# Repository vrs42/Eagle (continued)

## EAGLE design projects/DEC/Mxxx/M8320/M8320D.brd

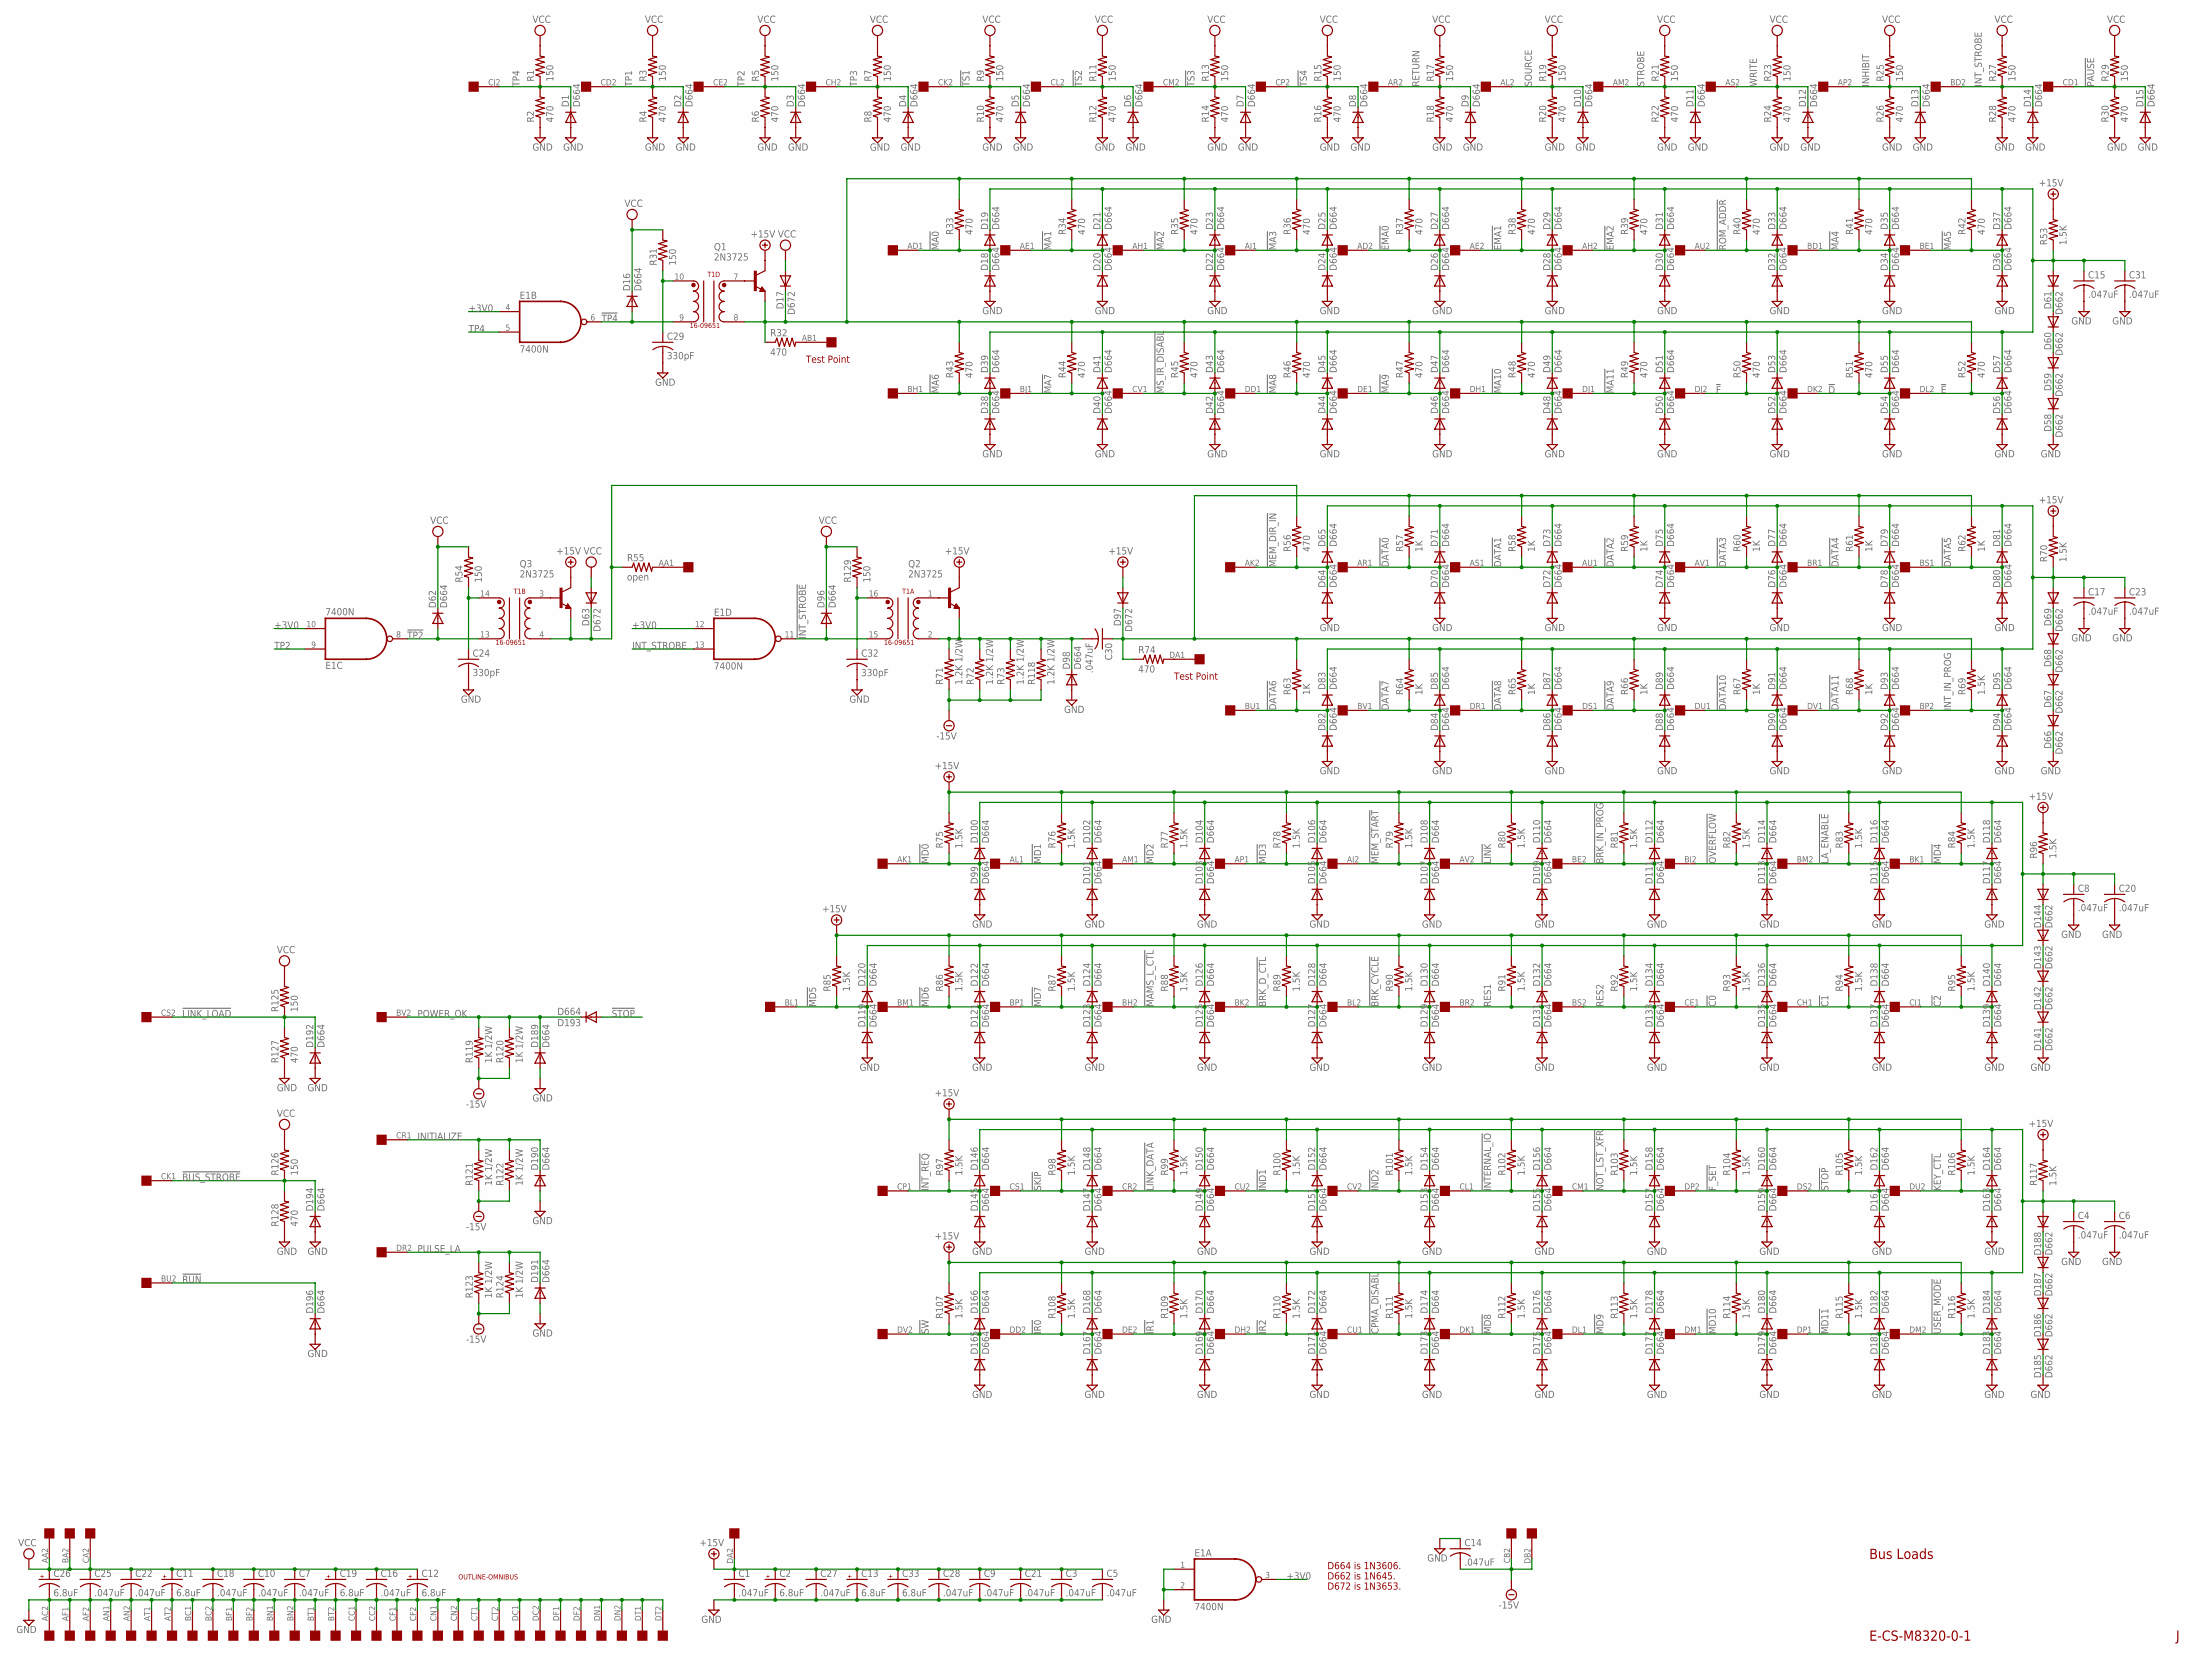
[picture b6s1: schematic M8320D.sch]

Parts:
C1, C3, C4, C5, C6, C7, C8, C9, C10, C14, C15, C16, C17, C18, C20, C21, C22, C23, C25, C27, C28, C30, C31: .047uF; C063-025X075
C2, C11, C12, C13, C19, C26, C33: 6.8uF; E12-8
C24, C29, C32: 330pF; C063-025X075
D1, D2, D3, D4, D5, D6, D7, D8, D9, D10, D11, D12, D13, D14, D15, D16, D18, D19, D20, D21, D22, D23, D24, D25, D26, D27, D28, D29, D30, D31, D32, D33, D34, D35, D36, D37, D38, D39, D40, D41, D42, D43, D44, D45, D46, D47, D48, D49, D50, D51, D52, D53, D54, D55, D56, D57, D62, D64, D65, D70, D71, D72, D73, D74, D75, D76, D77, D78, D79, D80, D81, D82, D83, D84, D85, D86, D87, D88, D89, D90, D91, D92, D93, D94, D95, D96, D98, D99, D100, D101, D102, D103, D104, D105, D106, D107, D108, D109, D110, D111, D112, D113, D114, D115, D116, D117, D118, D119, D120, D121, D122, D123, D124, D125, D126, D127, D128, D129, D130, D131, D132, D133, D134, D135, D136, D137, D138, D139, D140, D145, D146, D147, D148, D149, D150, D151, D152, D153, D154, D155, D156, D157, D158, D159, D160, D161, D162, D163, D164, D165, D166, D167, D168, D169, D170, D171, D172, D173, D174, D175, D176, D177, D178, D179, D180, D181, D182, D183, D184, D189, D190, D191, D192, D193, D194, D196: D664; DO35-10
D17, D63, D97: D672; DO35-10
D58, D59, D60, D61, D66, D67, D68, D69, D141, D142, D143, D144, D185, D186, D187, D188: D662; DO35-10
E1: 7400N; DIL14
Q1, Q2, Q3: 2N3725; TO92-EBC
R1, R3, R5, R7, R9, R11, R13, R15, R17, R19, R21, R23, R25, R27, R29, R31, R54, R125, R126, R129: 150; 0207/10
R2, R4, R6, R8, R10, R12, R14, R16, R18, R20, R22, R24, R26, R28, R30, R32, R33, R34, R35, R36, R37, R38, R39, R40, R41, R42, R43, R44, R45, R46, R47, R48, R49, R50, R51, R52, R56, R74, R127, R128: 470; 0207/10
R53, R69, R70, R75, R76, R77, R78, R79, R80, R81, R82, R83, R84, R85, R86, R87, R88, R89, R90, R91, R92, R93, R94, R95, R96, R97, R98, R99, R100, R101, R102, R103, R104, R105, R106, R107, R108, R109, R110, R111, R112, R113, R114, R115, R116, R117: 1.5K; 0207/10
R55: open; 0207/10
R57, R58, R59, R60, R61, R62, R63, R64, R65, R66, R67, R68: 1K; 0207/10
R71, R72, R73, R118: 1.2K 1/2W; 0411/15
R119, R120, R121, R122, R123, R124: 1K 1/2W; 0411/15
T1: 16-09651; DIL16
U$1: OUTLINE-OMNIBUS; OMNIBUS
U$2: QUAD; EDGE-CON8

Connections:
!BRK_CYCLE: D129.C, D130.A, R90.1, U$2.BL2
!BRK_D_CTL: D127.C, D128.A, R89.1, U$2.BK2
!BRK_IN_PROG: D111.C, D112.A, R81.1, U$2.BE2
!BUS_STROBE: D194.C, R126.1, R128.2, U$2.CK1
!C0: D135.C, D136.A, R93.1, U$2.CE1
!C1: D137.C, D138.A, R94.1, U$2.CH1
!C2: D139.C, D140.A, R95.1, U$2.CJ1
!CPMA_DISABL: D173.C, D174.A, R111.1, U$2.CU1
!D: D54.C, D55.A, R51.1, U$2.DK2
!DATA0: D70.C, D71.A, R57.1, U$2.AR1
!DATA1: D72.C, D73.A, R58.1, U$2.AS1
!DATA2: D74.C, D75.A, R59.1, U$2.AU1
!DATA3: D76.C, D77.A, R60.1, U$2.AV1
!DATA4: D78.C, D79.A, R61.1, U$2.BR1
!DATA5: D80.C, D81.A, R62.1, U$2.BS1
!DATA6: D82.C, D83.A, R63.1, U$2.BU1
!DATA7: D84.C, D85.A, R64.1, U$2.BV1
!DATA8: D86.C, D87.A, R65.1, U$2.DR1
!DATA9: D88.C, D89.A, R66.1, U$2.DS1
!DATA10: D90.C, D91.A, R67.1, U$2.DU1
!DATA11: D92.C, D93.A, R68.1, U$2.DV1
!E: D56.C, D57.A, R52.1, U$2.DL2
!EMA0: D26.C, D27.A, R37.1, U$2.AD2
!EMA1: D28.C, D29.A, R38.1, U$2.AE2
!EMA2: D30.C, D31.A, R39.1, U$2.AH2
!F: D52.C, D53.A, R50.1, U$2.DJ2
!F_SET: D159.C, D160.A, R104.1, U$2.DP2
!IND1: D151.C, D152.A, R100.1, U$2.CU2
!IND2: D153.C, D154.A, R101.1, U$2.CV2
!INTERNAL_IO: D155.C, D156.A, R102.1, U$2.CL1
!INT_REQ: D145.C, D146.A, R97.1, U$2.CP1
!INT_STROBE: D96.A, E1.11 (O), T1.15
!IR0: D167.C, D168.A, R108.1, U$2.DD2
!IR1: D169.C, D170.A, R109.1, U$2.DE2
!IR2: D171.C, D172.A, R110.1, U$2.DH2
!KEY_CTL: D163.C, D164.A, R106.1, U$2.DU2
!LA_ENABLE: D115.C, D116.A, R83.1, U$2.BM2
!LINK: D109.C, D110.A, R80.1, U$2.AV2
!LINK_DATA: D149.C, D150.A, R99.1, U$2.CR2
!LINK_LOAD: D192.C, R125.1, R127.2, U$2.CS2
!MA0: D18.C, D19.A, R33.1, U$2.AD1
!MA1: D20.C, D21.A, R34.1, U$2.AE1
!MA2: D22.C, D23.A, R35.1, U$2.AH1
!MA3: D24.C, D25.A, R36.1, U$2.AJ1
!MA4: D34.C, D35.A, R41.1, U$2.BD1
!MA5: D36.C, D37.A, R42.1, U$2.BE1
!MA6: D38.C, D39.A, R43.1, U$2.BH1
!MA7: D40.C, D41.A, R44.1, U$2.BJ1
!MA8: D44.C, D45.A, R46.1, U$2.DD1
!MA9: D46.C, D47.A, R47.1, U$2.DE1
!MA10: D48.C, D49.A, R48.1, U$2.DH1
!MA11: D50.C, D51.A, R49.1, U$2.DJ1
!MAMS_L_CTL: D125.C, D126.A, R88.1, U$2.BH2
!MD0: D99.C, D100.A, R75.1, U$2.AK1
!MD1: D101.C, D102.A, R76.1, U$2.AL1
!MD2: D103.C, D104.A, R77.1, U$2.AM1
!MD3: D105.C, D106.A, R78.1, U$2.AP1
!MD4: D117.C, D118.A, R84.1, U$2.BK1
!MD5: D119.C, D120.A, R85.1, U$2.BL1
!MD6: D121.C, D122.A, R86.1, U$2.BM1
!MD7: D123.C, D124.A, R87.1, U$2.BP1
!MD8: D175.C, D176.A, R112.1, U$2.DK1
!MD9: D177.C, D178.A, R113.1, U$2.DL1
!MD10: D179.C, D180.A, R114.1, U$2.DM1
!MD11: D181.C, D182.A, R115.1, U$2.DP1
!MEM_DIR_IN: D64.C, D65.A, R56.1, U$2.AK2
!MEM_START: D107.C, D108.A, R79.1, U$2.AJ2
!MS_IR_DISABL: D42.C, D43.A, R45.1, U$2.CV1
!NOT_LST_XFR: D157.C, D158.A, R103.1, U$2.CM1
!OVERFLOW: D113.C, D114.A, R82.1, U$2.BJ2
!PAUSE: D15.C, R29.1, R30.2, U$2.CD1
!ROM_ADDR: D32.C, D33.A, R40.1, U$2.AU2
!RUN: D196.C, U$2.BU2
!SKIP: D147.C, D148.A, R98.1, U$2.CS1
!STOP: D161.C, D162.A, D193.A, R105.1, U$2.DS2
!SW: D165.C, D166.A, R107.1, U$2.DV2
!TP2: D62.A, E1.8 (O), T1.13
!TP4: D16.A, E1.6 (O), T1.9
!TS1: D5.C, R9.1, R10.2, U$2.CK2
!TS2: D6.C, R11.1, R12.2, U$2.CL2
!TS3: D7.C, R13.1, R14.2, U$2.CM2
!TS4: D8.C, R15.1, R16.2, U$2.CP2
!USER_MODE: D183.C, D184.A, R116.1, U$2.DM2
+3V0: E1.3 (O), E1.4 (I0), E1.10 (I1), E1.12 (I0)
+15V: C1.1, C2.+, C3.1, C5.1, C9.1, C13.+, C21.1, C27.1, C28.1, C33.+, D97.A, Q1.C, Q2.C, Q3.C, R53.2, R70.2, R75.2, R76.2, R77.2, R78.2, R79.2, R80.2, R81.2, R82.2, R83.2, R84.2, R85.2, R86.2, R87.2, R88.2, R89.2, R90.2, R91.2, R92.2, R93.2, R94.2, R95.2, R96.2, R97.2, R98.2, R99.2, R100.2, R101.2, R102.2, R103.2, R104.2, R105.2, R106.2, R107.2, R108.2, R109.2, R110.2, R111.2, R112.2, R113.2, R114.2, R115.2, R116.2, R117.2, U$2.DA2
-15V: C14.2, R71.1, R72.1, R73.1, R118.1, R119.1, R120.1, R121.1, R122.1, R123.1, R124.1, U$2.CB2, U$2.DB2
GND: C1.2, C2.-, C3.2, C4.2, C5.2, C6.2, C7.2, C8.2, C9.2, C10.2, C11.-, C12.-, C13.-, C14.1, C15.2, C16.2, C17.2, C18.2, C19.-, C20.2, C21.2, C22.2, C23.2, C24.2, C25.2, C26.-, C27.2, C28.2, C29.2, C31.2, C32.2, C33.-, D1.A, D2.A, D3.A, D4.A, D5.A, D6.A, D7.A, D8.A, D9.A, D10.A, D11.A, D12.A, D13.A, D14.A, D15.A, D18.A, D20.A, D22.A, D24.A, D26.A, D28.A, D30.A, D32.A, D34.A, D36.A, D38.A, D40.A, D42.A, D44.A, D46.A, D48.A, D50.A, D52.A, D54.A, D56.A, D58.C, D64.A, D66.C, D70.A, D72.A, D74.A, D76.A, D78.A, D80.A, D82.A, D84.A, D86.A, D88.A, D90.A, D92.A, D94.A, D98.A, D99.A, D101.A, D103.A, D105.A, D107.A, D109.A, D111.A, D113.A, D115.A, D117.A, D119.A, D121.A, D123.A, D125.A, D127.A, D129.A, D131.A, D133.A, D135.A, D137.A, D139.A, D141.C, D145.A, D147.A, D149.A, D151.A, D153.A, D155.A, D157.A, D159.A, D161.A, D163.A, D165.A, D167.A, D169.A, D171.A, D173.A, D175.A, D177.A, D179.A, D181.A, D183.A, D185.C, D189.A, D190.A, D191.A, D192.A, D194.A, D196.A, E1.1 (I0), E1.2 (I1), E1.7 (GND), R2.1, R4.1, R6.1, R8.1, R10.1, R12.1, R14.1, R16.1, R18.1, R20.1, R22.1, R24.1, R26.1, R28.1, R30.1, R127.1, R128.1, U$2.AC2, U$2.AF1, U$2.AF2, U$2.AN1, U$2.AN2, U$2.AT1, U$2.AT2, U$2.BC1, U$2.BC2, U$2.BF1, U$2.BF2, U$2.BN1, U$2.BN2, U$2.BT1, U$2.BT2, U$2.CC1, U$2.CC2, U$2.CF1, U$2.CF2, U$2.CN1, U$2.CN2, U$2.CT1, U$2.CT2, U$2.DC1, U$2.DC2, U$2.DF1, U$2.DF2, U$2.DN1, U$2.DN2, U$2.DT1, U$2.DT2
INHIBIT: D13.C, R25.1, R26.2, U$2.AP2
INITIALIZE: D190.C, R121.2, R122.2, U$2.CR1
INT_IN_PROG: D94.C, D95.A, R69.1, U$2.BP2
INT_STROBE: D14.C, E1.13 (I1), R27.1, R28.2, U$2.BD2
unnamed: D58.A, D59.C
unnamed: D59.A, D60.C
unnamed: D60.A, D61.C
unnamed: C24.1, R54.1, T1.14
unnamed: Q3.B, T1.3
unnamed: C30.1, D97.C, R57.2, R58.2, R59.2, R60.2, R61.2, R62.2, R63.2, R64.2, R65.2, R66.2, R67.2, R68.2, R69.2, R74.1
unnamed: C32.1, R129.1, T1.16
unnamed: Q2.B, T1.1
unnamed: C15.1, C31.1, D19.C, D21.C, D23.C, D25.C, D27.C, D29.C, D31.C, D33.C, D35.C, D37.C, D39.C, D41.C, D43.C, D45.C, D47.C, D49.C, D51.C, D53.C, D55.C, D57.C, D61.A, R53.1
unnamed: D66.A, D67.C
unnamed: D67.A, D68.C
unnamed: D68.A, D69.C
unnamed: C17.1, C23.1, D65.C, D69.A, D71.C, D73.C, D75.C, D77.C, D79.C, D81.C, D83.C, D85.C, D87.C, D89.C, D91.C, D93.C, D95.C, R70.1
unnamed: C30.2, D98.C, Q2.E, R71.2, R72.2, R73.2, R118.2, T1.2
unnamed: D63.C, Q3.E, R55.1, R56.2, T1.4
unnamed: R74.2, U$2.DA1
unnamed: D185.A, D186.C
unnamed: D141.A, D142.C
unnamed: D142.A, D143.C
unnamed: D143.A, D144.C
unnamed: C29.1, R31.1, T1.10
unnamed: Q1.B, T1.7
unnamed: D17.C, Q1.E, R32.1, R33.2, R34.2, R35.2, R36.2, R37.2, R38.2, R39.2, R40.2, R41.2, R42.2, R43.2, R44.2, R45.2, R46.2, R47.2, R48.2, R49.2, R50.2, R51.2, R52.2, T1.8
unnamed: R32.2, U$2.AB1
unnamed: C8.1, C20.1, D100.C, D102.C, D104.C, D106.C, D108.C, D110.C, D112.C, D114.C, D116.C, D118.C, D120.C, D122.C, D124.C, D126.C, D128.C, D130.C, D132.C, D134.C, D136.C, D138.C, D140.C, D144.A, R96.1
unnamed: D186.A, D187.C
unnamed: D187.A, D188.C
unnamed: C4.1, C6.1, D146.C, D148.C, D150.C, D152.C, D154.C, D156.C, D158.C, D160.C, D162.C, D164.C, D166.C, D168.C, D170.C, D172.C, D174.C, D176.C, D178.C, D180.C, D182.C, D184.C, D188.A, R117.1
unnamed: R55.2, U$2.AA1
POWER_OK: D189.C, D193.C, R119.2, R120.2, U$2.BV2
PULSE_LA: D191.C, R123.2, R124.2, U$2.DR2
RES1: D131.C, D132.A, R91.1, U$2.BR2
RES2: D133.C, D134.A, R92.1, U$2.BS2
RETURN: D9.C, R17.1, R18.2, U$2.AR2
SOURCE: D10.C, R19.1, R20.2, U$2.AL2
STROBE: D11.C, R21.1, R22.2, U$2.AM2
TP1: D2.C, R3.1, R4.2, U$2.CD2
TP2: D3.C, E1.9 (I0), R5.1, R6.2, U$2.CE2
TP3: D4.C, R7.1, R8.2, U$2.CH2
TP4: D1.C, E1.5 (I1), R1.1, R2.2, U$2.CJ2
VCC: C7.1, C10.1, C11.+, C12.+, C16.1, C18.1, C19.+, C22.1, C25.1, C26.+, D16.C, D17.A, D62.C, D63.A, D96.C, E1.14 (VCC), R1.2, R3.2, R5.2, R7.2, R9.2, R11.2, R13.2, R15.2, R17.2, R19.2, R21.2, R23.2, R25.2, R27.2, R29.2, R31.2, R54.2, R125.2, R126.2, R129.2, U$2.AA2, U$2.BA2, U$2.CA2
WRITE: D12.C, R23.1, R24.2, U$2.AS2

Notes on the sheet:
E-CS-M8320-0-1
Bus Loads
D664 is 1N3606.
D672 is 1N3653.
D662 is 1N645.
Test Point

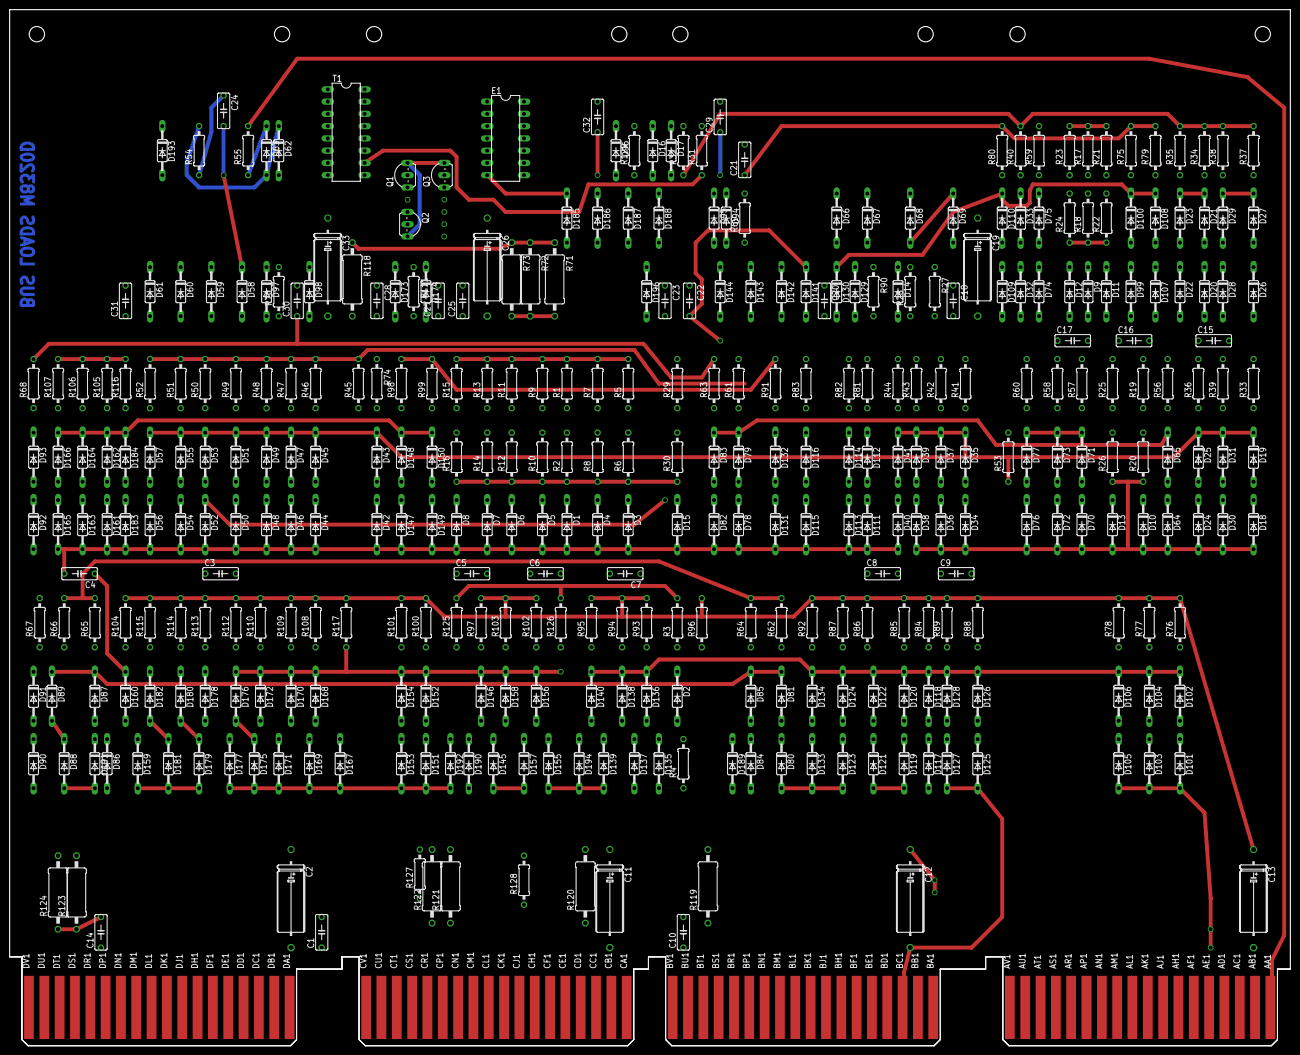
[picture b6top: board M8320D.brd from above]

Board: 2 copper layers, 265.3 x 214.6 mm, 364 parts (0 on the bottom side), 133 nets.
